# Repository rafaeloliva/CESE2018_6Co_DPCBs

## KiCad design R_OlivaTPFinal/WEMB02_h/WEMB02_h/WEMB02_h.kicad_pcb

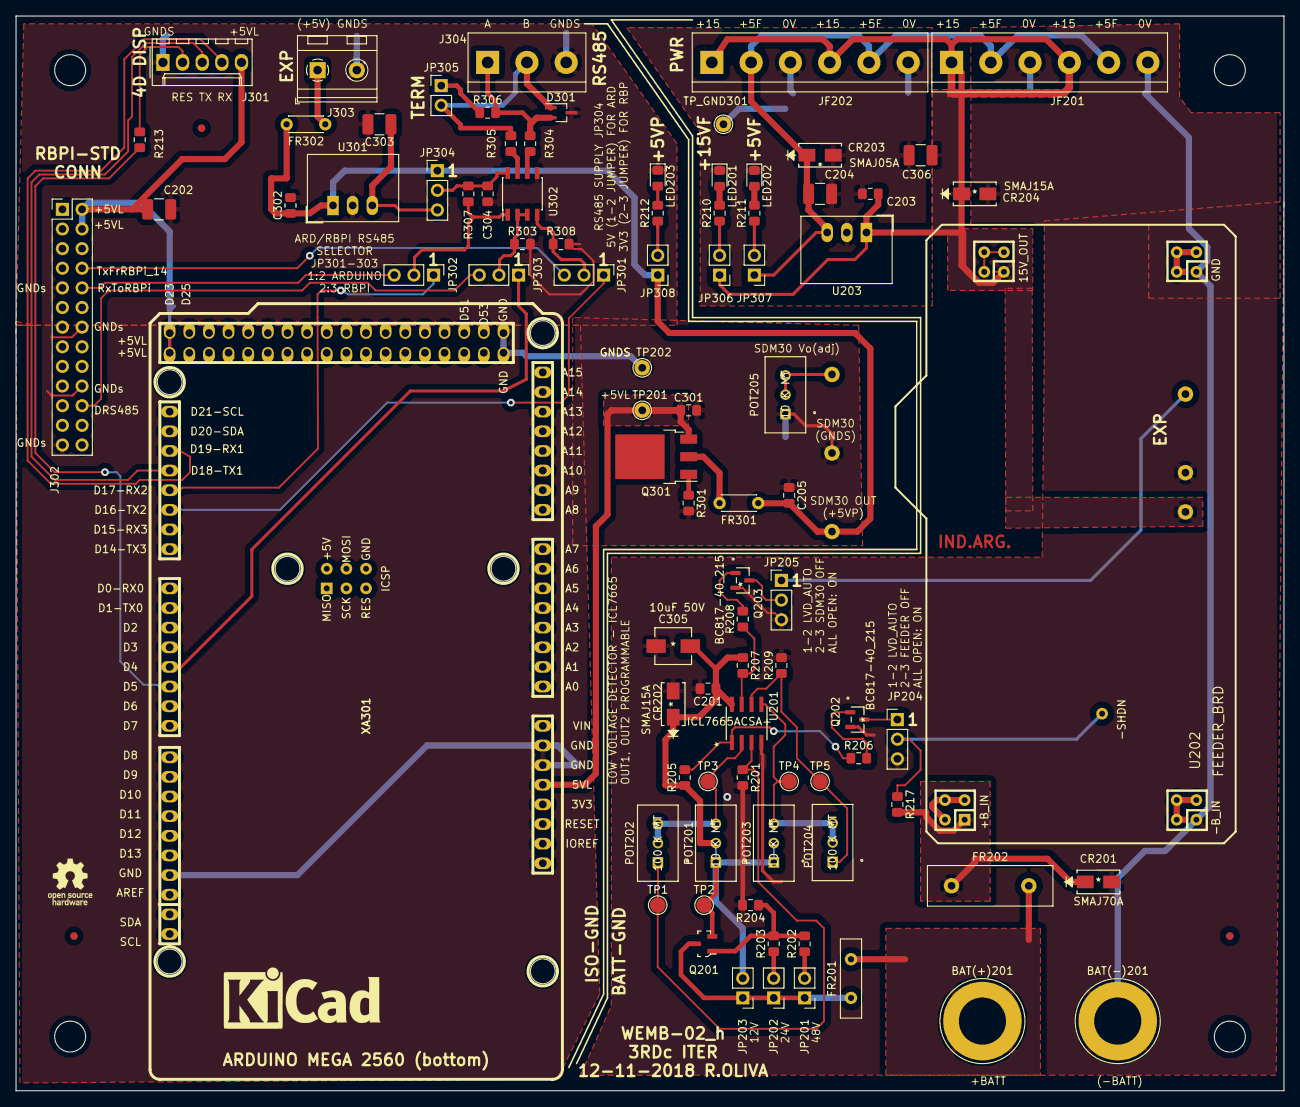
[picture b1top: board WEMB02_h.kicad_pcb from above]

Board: 2 copper layers, 164.0 x 139.0 mm, 96 parts (1 on the bottom side), 55 nets.

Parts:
BAT(+)201: SCREW_TERM8191; Banana_Jack_1Pin
BAT(-)201: SCREW_TERM8191; Banana_Jack_1Pin
C201, C205, C301, C304: 0.1uF 50V; C_0805_2012Metric_Pad1.15x1.40mm_HandSolder
C202: 4.7uF 50V MLCC; C_1210_3225Metric_Pad1.42x2.65mm_HandSolder
C203, C302: 0.1uF 50V MLCC; C_0805_2012Metric_Pad1.15x1.40mm_HandSolder
C204, C303: 10uF 50V MLCC; C_1210_3225Metric_Pad1.42x2.65mm_HandSolder
C305: 10uF 50V; EEE-1EA100WR
C306: 10uF 50V; C_1210_3225Metric_Pad1.42x2.65mm_HandSolder
CR201: SMAJ70A
CR202, CR204: SMAJ15A; SMAJ70A
CR203: SMAJ05A; SMAJ70A
D301: CDSOT23-SM712; SOT-323_SC-70_Handsoldering
F101, F102, F103: Fiducial; Fiducial_1mm_Dia_2mm_Outer
FR201: 0.25 A; C_Disc_D10.0mm_W2.5mm_P5.00mm
FR202: 2.7 A; C_Disc_D16.0mm_W5.0mm_P10.00mm
FR301, FR302: 1.5A; C_Disc_D4.3mm_W1.9mm_P5.00mm
J301: Conn_01x05; Molex_KK-254_AE-6410-05A_1x05_P2.54mm_Vertical
J302: RasPI_IO_Header; PinHeader_2x13_P2.54mm_Vertical
J303: EXP_PWR; TerminalBlock_RND_205-00232_1x02_P5.08mm_Horizontal
J304: RS485; TerminalBlock_bornier-3_P5.08mm
JF201, JF202: Screw_Terminal_01x06; TerminalBlock_bornier-6_P5.08mm
JP201: 48V; PinHeader_1x02_P2.54mm_Vertical
JP202: 24V; PinHeader_1x02_P2.54mm_Vertical
JP203: 12V; PinHeader_1x02_P2.54mm_Vertical
JP204, JP205: MAN/-AUTO; PinHeader_1x03_P2.54mm_Vertical
JP301: TX_FROM RBPI/ARD; PinHeader_1x03_P2.54mm_Vertical
JP302: RX TO RBPI/ARD; PinHeader_1x03_P2.54mm_Vertical
JP303: DIR_485 FROM RBPI/ARD; PinHeader_1x03_P2.54mm_Vertical
JP304: +3V3RBPI/+5VARD; PinHeader_1x03_P2.54mm_Vertical
JP305: TER; PinHeader_1x02_P2.54mm_Vertical
JP306, JP307, JP308: Jumper_2_Open; PinHeader_1x02_P2.54mm_Vertical
LED201, LED202, LED203: +5V_F ON; LED_0805_2012Metric_Pad1.15x1.40mm_HandSolder
MH101, MH102, MH103, MH104: MH4mm; MountingHole_4mm
POT201, POT203, POT205: 10 K MT; PV36W103C01B00
POT202, POT204: 100 K MT; PV36W103C01B00
Q201: MMBTA42LT1G; SOT-23-3
Q202, Q203: BC817-40_215; BC817-40
Q301: IRFR9024; TO-252-3_TabPin4
R201, R205, R206, R207, R208, R209, R210, R303, R307, R308: 10K; R_0805_2012Metric_Pad1.15x1.40mm_HandSolder
R202: 150K; R_0805_2012Metric_Pad1.15x1.40mm_HandSolder
R203: 56K; R_0805_2012Metric_Pad1.15x1.40mm_HandSolder
R204: 47K; R_0805_2012Metric_Pad1.15x1.40mm_HandSolder
R211, R212: 5K; R_0805_2012Metric_Pad1.15x1.40mm_HandSolder
R213: 1K; R_0805_2012Metric_Pad1.15x1.40mm_HandSolder
R217, R301: 100K; R_0805_2012Metric_Pad1.15x1.40mm_HandSolder
R304, R305: 47R; R_0805_2012Metric_Pad1.15x1.40mm_HandSolder
R306: 120R; R_0805_2012Metric_Pad1.15x1.40mm_HandSolder
TP1: TP1; TestPoint_Pad_D2.0mm
TP2, TP3, TP4, TP5: TP2; TestPoint_Pad_D2.0mm
TP201: +5VLtp; TestPoint_THTPad_D2.0mm_Drill1.0mm
TP202: GNDS; TestPoint_THTPad_D2.0mm_Drill1.0mm
TP_GND301: TP2; TestPoint_THTPad_D2.0mm_Drill1.0mm
U201: ICL7665ACSA+; ICL7665ACSA&plus_
U202: FEEDER_BRD; Global_feeder
U203: R-78E5.0-1.0; Converter_DCDC_RECOM_R-78E-0.5_THT
U204: SDM30-125S; POWER_SDM1b
U301: R-78E3.3-0.5; Converter_DCDC_RECOM_R-78E-0.5_THT
U302: SN75HVD08; SOIC-8_3.9x4.9mm_P1.27mm
XA301: Arduino_Mega2560_Shield; arduino_mega_header

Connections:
+5F: C204.1, CR203.1, JF201.2, JF201.5, JF202.2, JF202.5, JP307.1, U203.3
+5VL: C202.1, C301.1, J301.5, J302.2, J302.4, Q301.3, TP201.1, XA301.5, XA301.42, XA301.60
+5VP: C205.2, C302.1, FR301.1, FR302.2, JP304.1, JP308.1, U204.6, U301.1
+15V: C203.1, C306.1, CR204.1, JF201.1, JF201.4, JF202.1, JF202.4, JP306.1, U202.4, U203.1, U204.1
/DataComm/A_OUT: D301.2, J304.1, R304.1, R306.2
/DataComm/B_OUT: R305.2, U302.7
/DataComm/D485_RBPI: J302.22, JP303.3
/DataComm/DIR_485_ARD: JP303.1, XA301.73
/DataComm/D_485: JP303.2, R303.1, U302.2, U302.3
/DataComm/RESET_4D: J301.2, R213.1
/DataComm/RX1_DISP: J301.4, XA301.63
/DataComm/RX2_ARD: JP302.1, XA301.65
/DataComm/RX_TO_RBPI: J302.10, JP302.3
/DataComm/TX1_DISP: J301.3, XA301.64
/DataComm/TX2_ARD: JP301.1, XA301.66
/DataComm/TX_FROM_RBPI(TX0_14): J302.8, JP301.3
/Power/+B_FEED: CR201.1, FR202.1, R217.2, U202.1
/Power/BAT+: BAT(+)201.1, FR201.2, FR202.2
/Power/HYST1_IN: POT201.3, POT202.2, POT202.3, TP3.1, U201.2
/Power/HYST2_IN: POT203.3, POT204.2, POT204.3, TP4.1, U201.5
/Power/OUT1_SIG: R205.2, R206.1, U201.1
/Power/OUT2_SIG: R207.2, R208.1, U201.7
/Power/SET1_IN: POT202.1, R201.1, TP1.1, U201.3
/Power/SET2_IN: POT204.1, R209.1, TP5.1, U201.6
/Power/V+_Q_EMIT: C201.1, C305.1, CR202.1, JP203.2, POT201.1, POT201.2, POT203.1, POT203.2, Q201.2, R205.1, R207.1, TP2.1, U201.8
Earth: BAT(-)201.1, C201.2, C203.2, C204.2, C305.2, C306.2, CR201.2, CR202.2, CR203.2, CR204.2, JF201.3, JF201.6, JF202.3, JF202.6, JP204.3, JP205.3, LED201.1, LED202.1, Q202.2, Q203.2, R201.2, R204.2, R209.2, TP_GND301.1, U201.4, U202.2, U202.5, U203.2, U204.2
GNDS: C202.2, C205.1, C301.2, C302.2, C303.2, C304.2, D301.3, J301.1, J302.9, J302.14, J302.20, J302.25, J303.2, J304.3, LED203.1, POT205.1, R301.2, R303.2, R308.2, TP202.1, U204.7, U301.2, U302.5, XA301.6, XA301.7, XA301.25, XA301.43, XA301.83
unnamed: C303.1, JP304.3, U301.3
unnamed: C304.1, JP304.2, R307.1, U302.8
unnamed: D301.1, J304.2, JP305.2, R305.1
unnamed: FR201.1, JP201.1, JP202.1, JP203.1, Q201.3
unnamed: FR301.2, Q301.2
unnamed: FR302.1, J303.1
unnamed: JP201.2, R202.1
unnamed: JP202.2, R203.1
unnamed: JP204.1, Q202.3
unnamed: JP204.2, R217.1, U202.3
unnamed: JP205.1, U204.4
unnamed: JP205.2, Q203.3
unnamed: JP301.2, R308.1, U302.4
unnamed: JP302.2, R307.2, U302.1
unnamed: JP305.1, R306.1
unnamed: JP306.2, R210.1
unnamed: JP307.2, R211.1
unnamed: JP308.2, R212.1
unnamed: LED201.2, R210.2
unnamed: LED202.2, R211.2
unnamed: LED203.2, R212.2
unnamed: POT205.2, POT205.3, U204.8
unnamed: Q201.1, R202.2, R203.2, R204.1
unnamed: Q202.1, R206.2
unnamed: Q203.1, R208.2
unnamed: Q301.1, R301.1
unnamed: R213.2, XA301.74
unnamed: R304.2, U302.6

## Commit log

2018-10-05 Archivos Practica PCB + TPFinal agregados 5-10-18
2018-10-07 Add Ej3. 7-10-2018
2018-10-07 Add ej3 3d views
2018-10-11 Agregado v02b 11-10-2018 Esquematico solo y layout en PCB sin netlist
2018-10-11 Updated PCB layout - no netlist yet 11-10-18
2018-11-02 Version 02_e SCH terminado - PCB con componentes ubicados aproximadamente
2018-11-07 Revision WEMB02_f: Distribucion en PCB ok, comienzo ruteo
2018-11-12 V02g Ruteado completo, pocos ERC, faltan algunos 3D
2018-11-14 Version 02h con correcciones 14.11.18 luego de revision de R.Compañy - Agregados DOCs y Datasheets
2018-12-08 SCH Version 02j finalizado, corrigiendo PCB según indicacion Docente
2018-12-09 WEMB02-J Sch + PCB completos, faltan algunos mod.3D
2018-12-14 Ultimas Modificaciones WEMB02-j 14.12.2018 3D & Logos added

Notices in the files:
parts and their libraries:
Copyright 2016 Accelerated Designs. All rights reserved.
